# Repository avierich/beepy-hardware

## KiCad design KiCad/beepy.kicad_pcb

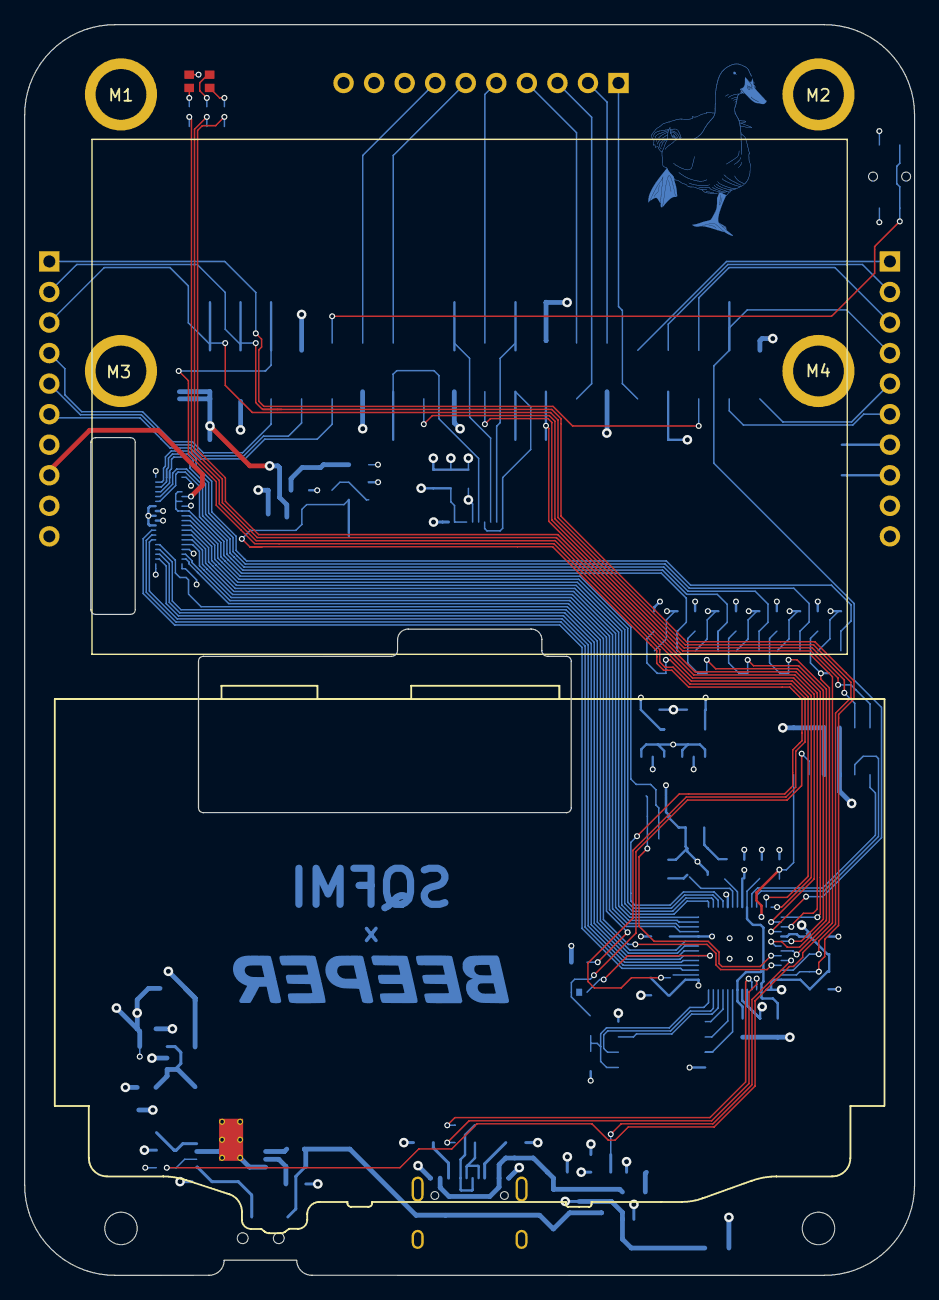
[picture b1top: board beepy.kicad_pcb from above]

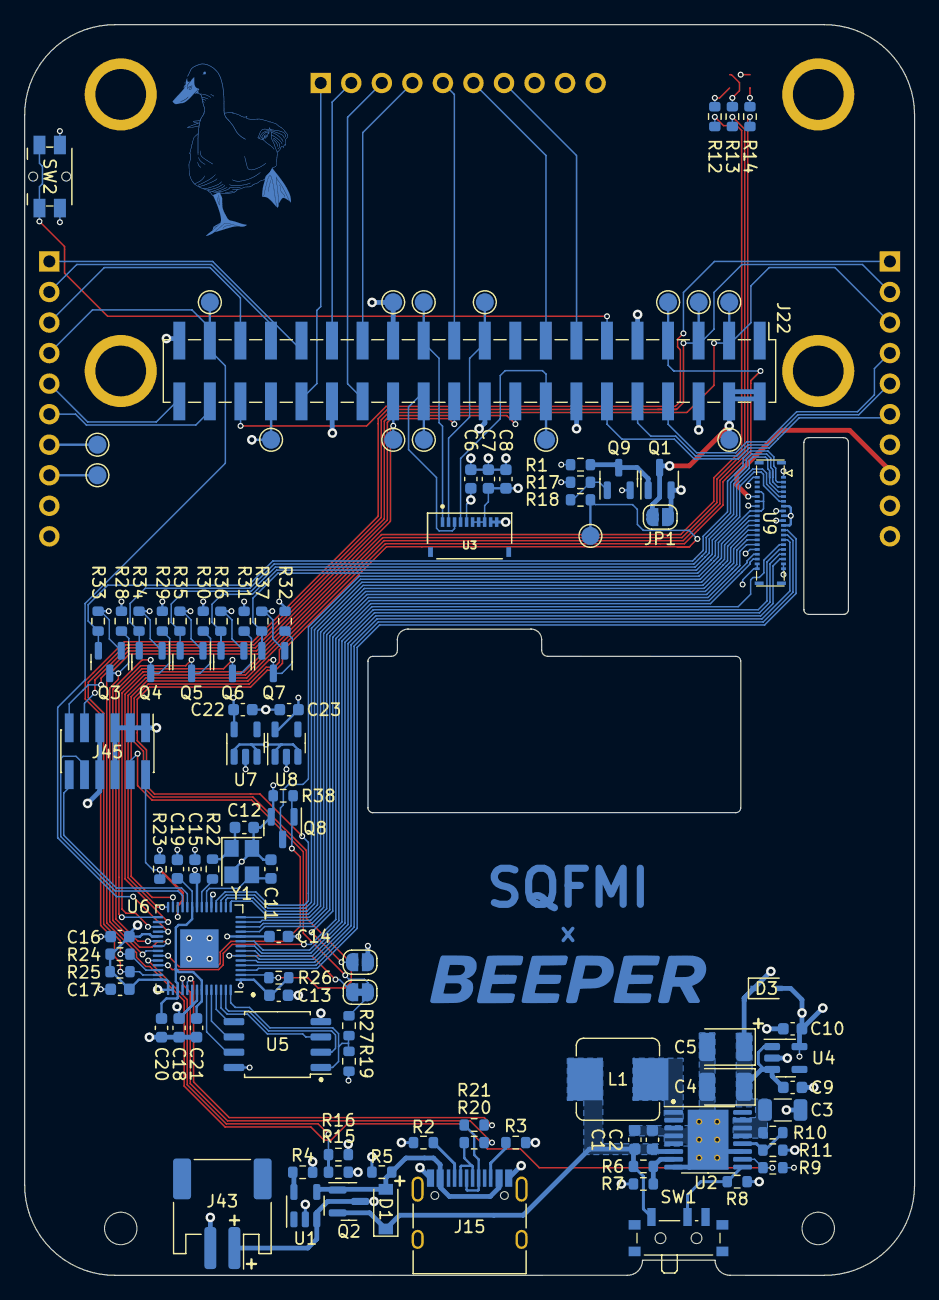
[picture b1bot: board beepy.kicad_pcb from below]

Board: 4 copper layers, 74.0 x 104.0 mm, 118 parts (115 on the bottom side), 100 nets.

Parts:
C1, C9, C10: 10uF; C_0603_1608Metric
C2, C6, C8: 100nF; C_0603_1608Metric
C3: 22uF; C_1206_3216Metric
C4, C5: 100uF; CP_EIA-3528-15_AVX-H
C7, C18, C21: 1uF; C_0603_1608Metric
C11, C12: 12pF; C_0603_1608Metric
C13, C14, C15, C16, C17, C19, C20, C22, C23: 0.1uF; C_0603_1608Metric
D1: B5819W; D_SOD-123
D2: Notification LED; FM-B2020RGBA-HG
D3: D_Schottky_Small; D_SOD-323
H1, H2: MountingHole; MountingHole_2.7mm_M2.5
J15: USB_C_Receptacle_USB2.0; USB_C_Receptacle_HRO_TYPE-C-31-M-12
J22: Pi Zero; PinHeader_2x20_P2.54mm_Vertical_SMD
J43: Battery; JST_PH_S2B-PH-SM4-TB_1x02-1MP_P2.00mm_Horizontal
J44: Header 1; PinHeader_1x10_P2.54mm_Vertical
J45: PRG_HEADER; PinHeader_2x06_P1.27mm_Vertical_SMD
J46: Header 2; PinHeader_1x10_P2.54mm_Vertical
J47: Header 3; PinHeader_1x10_P2.54mm_Vertical
JP1: PI PWR; SolderJumper-2_P1.3mm_Open_RoundedPad1.0x1.5mm
JP2: BOOTSEL_JUMPER; SolderJumper-2_P1.3mm_Bridged_RoundedPad1.0x1.5mm
JP3: SJ_MIC_VDD; SolderJumper-2_P1.3mm_Open_RoundedPad1.0x1.5mm
L1: 6.8uH/4A; L_Bourns_SRP7028A_7.3x6.6mm
M1, M2, M3, M4: MountingHole_2.5mm_Pad
Q1, Q2: SI2301; SOT-23
Q3, Q4, Q5, Q6, Q7, Q8: BSS138; SOT-23
Q9: S8050; SOT-23
R1, R4, R17, R19, R23, R26, R28, R29, R30, R31, R32, R33, R34, R35, R36, R37, R38: 10K; R_0603_1608Metric
R2, R3: 5.1K; R_0603_1608Metric
R5, R8, R15, R16: 100K; R_0603_1608Metric
R6, R10: 2M; R_0603_1608Metric
R7: 360K; R_0603_1608Metric
R9: 1M; R_0603_1608Metric
R11: 220K; R_0603_1608Metric
R12: 220; R_0603_1608Metric
R13, R14: 100; R_0603_1608Metric
R18: 330; R_0603_1608Metric
R20, R21: 27R; R_0603_1608Metric
R22, R27: 1K; R_0603_1608Metric
R24, R25: 4.7K; R_0603_1608Metric
REFe: SQFMI-DUCK-LOGO; SQFMI-DUCK-LOGO-BCU
SW1: ON/OFF; SW_SPDT_PCM12
SW2: Button; Panasonic_EVQPUL_EVQPUC
TP1, TP4, TP5, TP6, TP7, TP8, TP9, TP10, TP11, TP12, TP13, TP14, TP15, TP16, TP17: TestPoint; TestPoint_Pad_D1.5mm
U1: TP4054; SOT-23-5
U2: TPS61090; HTSSOP-16-1EP_4.4x5mm_P0.65mm_EP3.4x5mm_Mask2.46x2.31mm_The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
U3: LS027B7DH01; HRS_FH34SRJ-10S-0.5SH(50)
U4: AP2112K-3.3; SOT-23-5
U5: W25Q16JVSSIQ; SSOP-8_5.25x5.24mm_P1.27mm
U6: RP2040; QFN-56-1EP_7x7mm_P0.4mm_EP5.6x5.6mm
U7: ME6212C18M5G; SOT-23-5
U8: ME6212C28M5G; SOT-23-5
U9: BBQ20KBD; BM20B(0.8)-40DS-0.4V
Y1: XYDBPCNANF-12MHZ; Crystal_SMD_3225-4Pin_3.2x2.5mm

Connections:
+1V8: C22.1, Q3.1 (G), Q4.1 (G), Q5.1 (G), Q6.1 (G), Q7.1 (G), R33.2, R34.2, R35.2, R36.2, R37.2, U7.5 (OUT), U9.10 (1V8)
+2V8: C23.1, U8.5 (OUT), U9.8 (2V8)
+3V3: C6.1, C10.2, C13.1, C14.1, C15.1, C16.1, C17.1, C18.1, D2.3 (A), D3.2 (A), J44.7, J45.7, J45.8, J46.8, J47.8, JP3.1 (A), R9.2, R19.2, R23.1, R24.2, R25.1, R26.1, R28.2, R29.2, R30.2, R31.2, R32.2, TP13.1, U3.5 (DISP), U4.5 (VOUT), U5.8 (VDD), U6.1 (IOVDD), U6.10 (IOVDD), U6.22 (IOVDD), U6.33 (IOVDD), U6.42 (IOVDD), U6.43 (ADC_AVDD), U6.44 (VREG_VIN), U6.48 (USB_VDD), U6.49 (IOVDD), U7.1 (IN), U7.3 (EN), U8.1 (IN), U8.3 (EN), U9.34 (LEDA), U9.36 (LEDA)
+5V: C3.1, C4.1, C5.1, C7.1, C8.1, C9.1, D3.1 (K), J44.8, J47.7, JP1.1 (A), Q1.2 (S), R1.1, R10.1, TP14.1, U2.13 (VOUT), U2.14 (VOUT), U2.15 (VOUT), U3.6 (VDDA), U3.7 (VDD), U3.8 (EXTMODE), U4.1 (VIN), U4.3 (EN)
+BATT: J43.1, Q2.3 (D), R15.1, U1.3 (VBAT)
/Button: J22.11 (GPIO17), SW2.1 (A)
/DISP_CS: J22.24 (~CE0/GPIO8), TP6.1, U3.3 (SCS)
/DISP_EXTIN: J22.16 (GPIO23), TP1.1, U3.4 (EXTCOMIN)
/DISP_SCLK: J22.23 (SCLK0/GPIO11), TP8.1, U3.1 (SCLK)
/DISP_SI: J22.19 (MOSI0/GPIO10), TP5.1, U3.2 (SI)
/LBO: J22.26 (~CE1/GPIO7), R9.1, TP9.1, U2.10 (LBO)
/PI_HEADER_SWCLK: J22.22 (GPIO25), J45.11
/PI_HEADER_SWDIO: J22.18 (GPIO24), J45.9
/Pi_GPIO0: J22.27 (ID_SD/GPIO0), J46.4
/Pi_GPIO1: J22.28 (ID_SC/GPIO1), J46.3
/Pi_GPIO5: J22.29 (GCLK1/GPIO5), J46.2
/Pi_GPIO6: J22.31 (GCLK2/GPIO6), J44.1
/Pi_GPIO09: J22.21 (MISO0/GPIO9), J46.5
/Pi_GPIO12: J22.32 (PWM0/GPIO12), J46.1
/Pi_GPIO13: J22.33 (PWM1/GPIO13), J44.2
/Pi_GPIO14: J22.8 (GPIO14/TXD), J47.4
/Pi_GPIO15: J22.10 (GPIO15/RXD), J47.5
/Pi_GPIO16: J22.36 (GPIO16), J47.1
/Pi_GPIO18: J22.12 (GPIO18/PWM0), J47.6
/Pi_GPIO19: J22.35 (GPIO19/MISO1), J44.3
/Pi_GPIO20: J22.38 (GPIO20/MOSI1), J44.6
/Pi_GPIO21: J22.40 (GPIO21/SCLK1), J44.5
/Pi_GPIO22: J22.15 (GPIO22), J46.6
/Pi_GPIO26: J22.37 (GPIO26), J44.4, TP17.1, U6.32 (GPIO21)
/Pi_GPIO27: J22.13 (GPIO27), J46.7
/Pi_INT: J22.7 (GCLK0/GPIO4), R26.2, TP7.1, U6.2 (GPIO0)
/Pi_PWR: R18.1, TP10.1, U6.18 (GPIO15)
/Pi_SCL: J22.5 (SCL/GPIO3), J47.2, R25.2, TP12.1, U6.41 (GPIO29)
/Pi_SDA: J22.3 (SDA/GPIO2), J47.3, R24.1, TP11.1, U6.40 (GPIO28)
/RP2040/BATT_ADC: R15.2, R16.1, U6.38 (GPIO26)
/RP2040/COL1: U6.3 (GPIO1), U9.12 (COL1)
/RP2040/COL2: U6.4 (GPIO2), U9.13 (COL2)
/RP2040/COL3: U6.5 (GPIO3), U9.14 (COL3)
/RP2040/COL4: U6.9 (GPIO7), U9.15 (COL4)
/RP2040/COL5: U6.8 (GPIO6), U9.16 (COL5)
/RP2040/COL6: U6.7 (GPIO5), U9.17 (COL6)
/RP2040/COL7: JP2.1 (A), U6.6 (GPIO4), U9.18 (COL7)
/RP2040/D+: R21.1, U6.47 (USB_D+)
/RP2040/D-: R20.1, U6.46 (USB_D-)
/RP2040/KB_BL: Q8.1 (G), R38.1, U6.37 (GPIO25)
/RP2040/Keyboard/TP_MOTION_1V8: Q5.2 (S), R35.1, U9.4 (TP_MOTION)
/RP2040/Keyboard/TP_RESET_1V8: Q7.2 (S), R37.1, U9.6 (TP_RESET)
/RP2040/Keyboard/TP_SCL_1V8: Q4.2 (S), R34.1, U9.3 (TP_SCL)
/RP2040/Keyboard/TP_SDA_1V8: Q6.2 (S), R36.1, U9.5 (TP_SDA)
/RP2040/Keyboard/TP_SHUTDOWN_1V8: Q3.2 (S), R33.1, U9.2 (TP_SHUTDOWN)
/RP2040/LED_B: R14.1, U6.28 (GPIO17)
/RP2040/LED_G: R13.1, U6.30 (GPIO19)
/RP2040/LED_R: R12.1, U6.31 (GPIO20)
/RP2040/MIC: U6.39 (GPIO27), U9.23 (MIC)
/RP2040/QSPI_SCLK: U5.6 (SCK), U6.52 (QSPI_SCLK)
/RP2040/QSPI_SD0: U5.5 (DI/IO0), U6.53 (QSPI_SD0)
/RP2040/QSPI_SD1: U5.2 (DO/IO1), U6.55 (QSPI_SD1)
/RP2040/QSPI_SD2: U5.3 (~WP~/IO2), U6.54 (QSPI_SD2)
/RP2040/QSPI_SD3: U5.7 (~HOLD~/IO3), U6.51 (QSPI_SD3)
/RP2040/ROW1: U6.17 (GPIO14), U9.32 (ROW1)
/RP2040/ROW2: U6.16 (GPIO13), U9.31 (ROW2)
/RP2040/ROW3: U6.15 (GPIO12), U9.30 (ROW3)
/RP2040/ROW4: U6.14 (GPIO11), U9.29 (ROW4)
/RP2040/ROW5: U6.13 (GPIO10), U9.28 (ROW5)
/RP2040/ROW6: U6.12 (GPIO9), U9.27 (ROW6)
/RP2040/ROW7: U6.11 (GPIO8), U9.26 (ROW7)
/RP2040/TP_MOTION: Q5.3 (D), R30.1, U6.34 (GPIO22)
/RP2040/TP_RESET: Q7.3 (D), R32.1, U6.27 (GPIO16)
/RP2040/TP_SCL: Q4.3 (D), R29.1, U6.35 (GPIO23)
/RP2040/TP_SDA: Q6.3 (D), R31.1, U6.29 (GPIO18)
/RP2040/TP_SHUTDOWN: Q3.3 (D), R28.1, U6.36 (GPIO24)
/RP2040/~QSPI_CS: R19.1, R27.2, U5.1 (~CS~), U6.56 (~QSPI_CS)
BOOTSEL: J45.4, JP2.2 (B), R27.1
GND: C1.2, C2.2, C3.2, C4.2, C5.2, C6.2, C7.2, C8.2, C9.2, C10.1, C11.2, C12.2, C13.2, C14.2, C15.2, C16.2, C17.2, C18.2, C19.2, C20.2, C21.2, C22.2, C23.2, J15.A1 (GND), J15.A12 (GND), J15.B1 (GND), J15.B12 (GND), J22.6 (GND), J22.9 (GND), J22.14 (GND), J22.20 (GND), J22.25 (GND), J22.30 (GND), J22.34 (GND), J22.39 (GND), J43.2, J44.9, J44.10, J45.1, J45.3, J45.5, J45.6, J46.9, J46.10, J47.9, J47.10, Q8.2 (S), Q9.2 (E), R2.1, R3.1, R4.1, R5.2, R7.2, R8.1, R11.2, R16.2, R17.1, R38.2, SW2.2 (B), TP15.1, TP16.1, U1.2 (VSS), U2.3 (PGND), U2.4 (PGND), U2.5 (PGND), U2.8 (SYNC), U2.11 (GND), U2.17 (PAD), U3.9 (VSS), U3.10 (VSSA), U4.2 (GND), U5.4 (GND), U6.19 (TESTEN), U6.57 (GND), U7.2 (GND), U8.2 (GND), U9.1 (GND), U9.7 (GND), U9.9 (GND), U9.11 (GND), U9.19 (GND), U9.20 (GND), U9.21 (GND), U9.22 (AGND), U9.25 (GND), U9.40 (GND), Y1.2, Y1.4
unnamed: C12.1, R22.2, Y1.1
unnamed: C1.1, C2.1, D1.1 (K), L1.1, Q2.2 (S), R6.1, SW1.1 (A), U2.6 (VBAT)
unnamed: D2.2 (BK), R14.2
unnamed: D2.4 (GK), R13.2
unnamed: D2.1 (RK), R12.2
unnamed: J15.A5 (CC1), R2.2
unnamed: J15.B5 (CC2), R3.2
unnamed: J22.2 (5V), J22.4 (5V), JP1.2 (B), Q1.3 (D), TP4.1
unnamed: JP3.2 (B), U9.24 (MIC_VDD)
unnamed: L1.2, U2.1 (SW), U2.2 (SW)
unnamed: Q1.1 (G), Q9.3 (C), R1.2
unnamed: Q8.3 (D), U9.33 (LEDK), U9.35 (LEDK), U9.37 (LEDK)
unnamed: Q9.1 (B), R17.2, R18.2
unnamed: R8.2, SW1.2 (B), U2.9 (EN)
unnamed: R4.2, U1.5 (PROG)
unnamed: R10.2, R11.1, U2.12 (FB)
unnamed: R6.2, R7.1, U2.7 (LBI)
unnamed: C19.1, C20.1, C21.1, U6.23 (DVDD), U6.45 (VREG_VOUT), U6.50 (DVDD)
unnamed: C11.1, U6.20 (XIN), Y1.3
unnamed: R22.1, U6.21 (XOUT)
SWCLK: J45.12, U6.24 (SWCLK)
SWDIO: J45.10, U6.25 (SWDIO)
USB_D+: J15.A6 (D+), J15.B6 (D+), R21.2
USB_D-: J15.A7 (D-), J15.B7 (D-), R20.2
VBUS: D1.2 (A), J15.A4 (VBUS), J15.A9 (VBUS), J15.B4 (VBUS), J15.B9 (VBUS), Q2.1 (G), R5.1, U1.4 (VDD)
~RESET: J45.2, R23.2, U6.26 (RUN)

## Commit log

2024-08-15 Importing to KiCAD 8 and using pin headers instead of springs
2024-08-15 Swapping NOR chip for equivalent
2024-08-15 Moving header designator
